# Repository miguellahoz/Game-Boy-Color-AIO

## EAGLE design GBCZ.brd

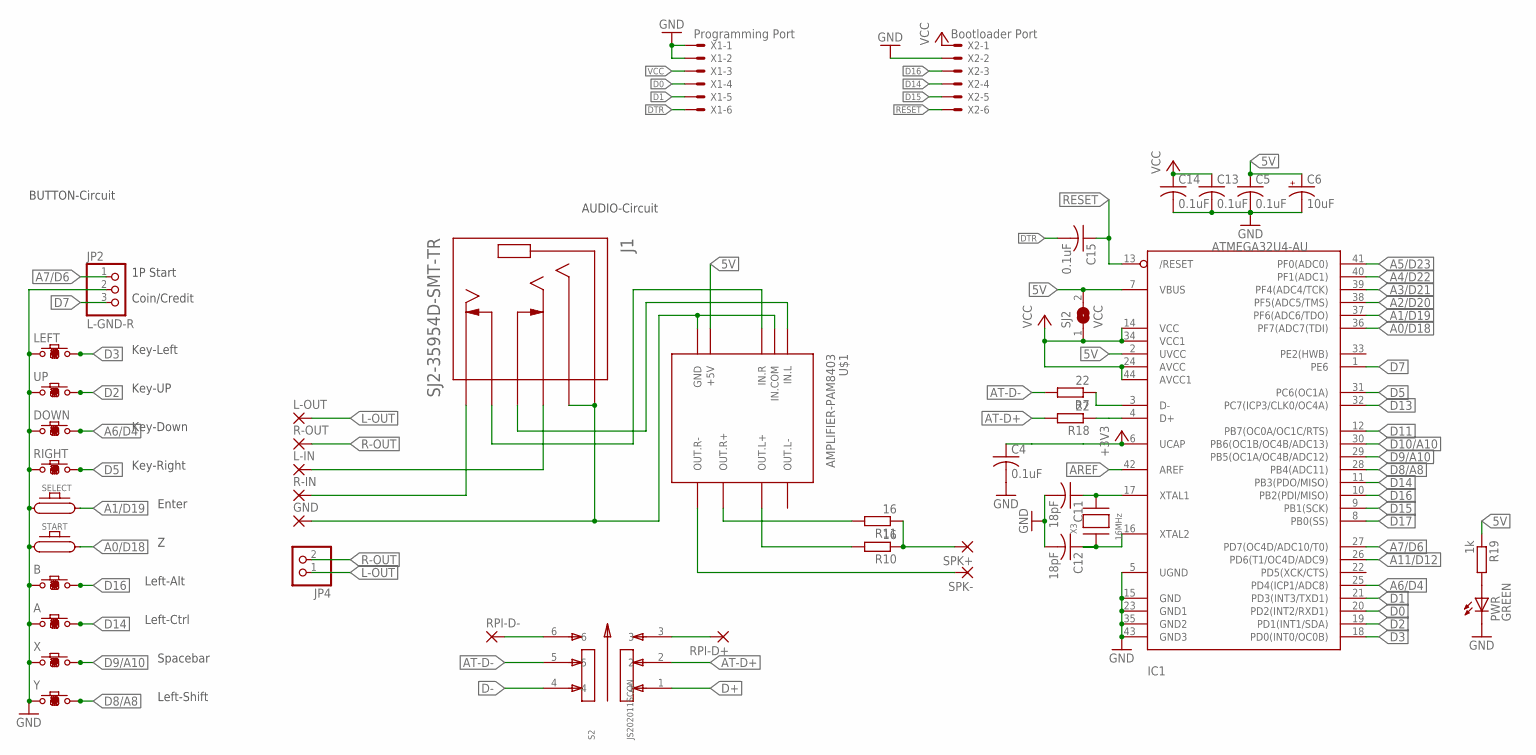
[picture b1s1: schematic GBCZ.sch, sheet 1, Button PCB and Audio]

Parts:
A: GBC_BTN
B: GBC_BTN
C4, C5, C13, C14, C15: 0.1uF; C0805K
C6: 10uF; A/3216-18R
C11, C12: 18pF; C0805K
DOWN: GBC_BTN
GND: WIREPADSMD1,27-254; SMD1,27-2,54
IC1: ATMEGA32U4-AU; TQFP44
J1: SJ2-35954D-SMT-TR; CUI_SJ2-35954D-SMT-TR
JP2: L-GND-R; 1X03
JP4: PINHD-1X2; 1X02
L-IN: WIREPADSMD1,27-254; SMD1,27-2,54
L-OUT: WIREPADSMD1,27-254; SMD1,27-2,54
LEFT: GBC_BTN
PWR: GREEN; CHIPLED_0805
R7, R18: 22; R0603
R10, R11: 16; R0603
R19: 1k; R0603
R-IN: WIREPADSMD1,27-254; SMD1,27-2,54
R-OUT: WIREPADSMD1,27-254; SMD1,27-2,54
RIGHT: GBC_BTN
RPI-D+: WIREPADSMD1,27-254; SMD1,27-2,54
RPI-D-: WIREPADSMD1,27-254; SMD1,27-2,54
S2: JS202011SCQN; SW_JS202011SCQN
SELECT: GBC_BTN_START
SJ2: VCC; SJ
SPK+: WIREPADSMD1,27-254; SMD1,27-2,54
SPK-: WIREPADSMD1,27-254; SMD1,27-2,54
START: GBC_BTN_START
U$1: AMPLIFIER-PAM8403
UP: GBC_BTN
X: GBC_BTN
X1: Programming Port; 22-23-2061
X2: Bootloader Port; 22-23-2061
X3: 16MHz; NX5032
Y: GBC_BTN

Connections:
5V: C5.1, C6.+, IC1.2 (UVCC), IC1.7 (VBUS), R19.1, SJ2.2, U$1.+5V; also elsewhere on the board
+3V3: C4.1, IC1.6 (UCAP)
A0/D18: IC1.36 (PF7(ADC7(TDI)), START.P$2
A1/D19: IC1.37 (PF6(ADC6/TDO)), SELECT.P$2
A2/D20: IC1.38 (PF5(ADC5/TMS))
A3/D21: IC1.39 (PF4(ADC4/TCK))
A4/D22: IC1.40 (PF1(ADC1))
A5/D23: IC1.41 (PF0(ADC0))
A6/D4: DOWN.P$2, IC1.25 (PD4(ICP1/ADC8))
A7/D6: IC1.27 (PD7(OC4D/ADC10/T0)), JP2.1
A11/D12: IC1.26 (PD6(T1/OC4D/ADC9))
AREF: IC1.42 (AREF)
AT-D+: R18.2, S2.2
AT-D-: R7.2, S2.5
D0: IC1.20 (PD2(INT2/RXD1)), X1.4
D1: IC1.21 (PD3(INT3/TXD1)), X1.5
D2: IC1.19 (PD1(INT1/SDA)), UP.P$2
D3: IC1.18 (PD0(INT0/OC0B)), LEFT.P$2
D5: IC1.31 (PC6(OC1A)), RIGHT.P$2
D7: IC1.1 (PE6), JP2.3
D8/A8: IC1.28 (PB4(ADC11)), Y.P$2
D9/A10: IC1.29 (PB5(OC1A/OC4B/ADC12)), X.P$2
D10/A10: IC1.30 (PB6(OC1B/OC4B/ADC13))
D11: IC1.12 (PB7(OC0A/OC1C/RTS))
D13: IC1.32 (PC7(ICP3/CLK0/OC4A))
D14: A.P$2, IC1.11 (PB3(PDO/MISO)), X2.4
D15: IC1.9 (PB1(SCK)), X2.5
D16: B.P$2, IC1.10 (PB2(PDI/MISO)), X2.3
D17: IC1.8 (PB0(SS))
D+: S2.1; also elsewhere on the board
D-: S2.4; also elsewhere on the board
DTR: C15.2, X1.6
GND: A.P$1, B.P$1, C4.2, C5.2, C6.-, C11.2, C12.2, C13.2, C14.2, DOWN.P$1, IC1.5 (UGND), IC1.15 (GND), IC1.23 (GND1), IC1.35 (GND2), IC1.43 (GND3), JP2.2, LEFT.P$1, PWR.C, RIGHT.P$1, SELECT.P$1, START.P$1, UP.P$1, X.P$1, X1.1, X1.2, X2.2, Y.P$1; also elsewhere on the board
L-OUT: JP4.1, L-OUT.1
unnamed: RPI-D-.1, S2.6
unnamed: RPI-D+.1, S2.3
unnamed: R11.2, U$1.OUT.R+
unnamed: GND.1, J1.1 (SLEEVE), J1.4 (RING2), U$1.GND, U$1.IN.COM
unnamed: J1.11 (RING1_SWITCH), U$1.IN.L
unnamed: J1.10 (TIP_SWITCH), U$1.IN.R
unnamed: J1.2 (TIP), R-IN.1
unnamed: J1.3 (RING1), L-IN.1
unnamed: R10.2, U$1.OUT.L+
unnamed: R10.1, R11.1, SPK+.1
unnamed: SPK-.1, U$1.OUT.R-
unnamed: IC1.3 (D-), R7.1
unnamed: IC1.4 (D+), R18.1
unnamed: C12.1, IC1.16 (XTAL2), X3.P$1
unnamed: C11.1, IC1.17 (XTAL1), X3.P$2
unnamed: PWR.A, R19.2
R-OUT: JP4.2, R-OUT.1
RESET: C15.1, IC1.13 (/RESET), X2.6
VCC: C13.1, C14.1, IC1.14 (VCC), IC1.24 (AVCC), IC1.34 (VCC1), IC1.44 (AVCC1), SJ2.1, X1.3; also elsewhere on the board

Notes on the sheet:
AUDIO-Circuit
BUTTON-Circuit
Key-UP
Key-Left
Key-Down
Key-Right
Left-Ctrl
Left-Alt
Spacebar
Left-Shift
Enter
Coin/Credit
1P Start

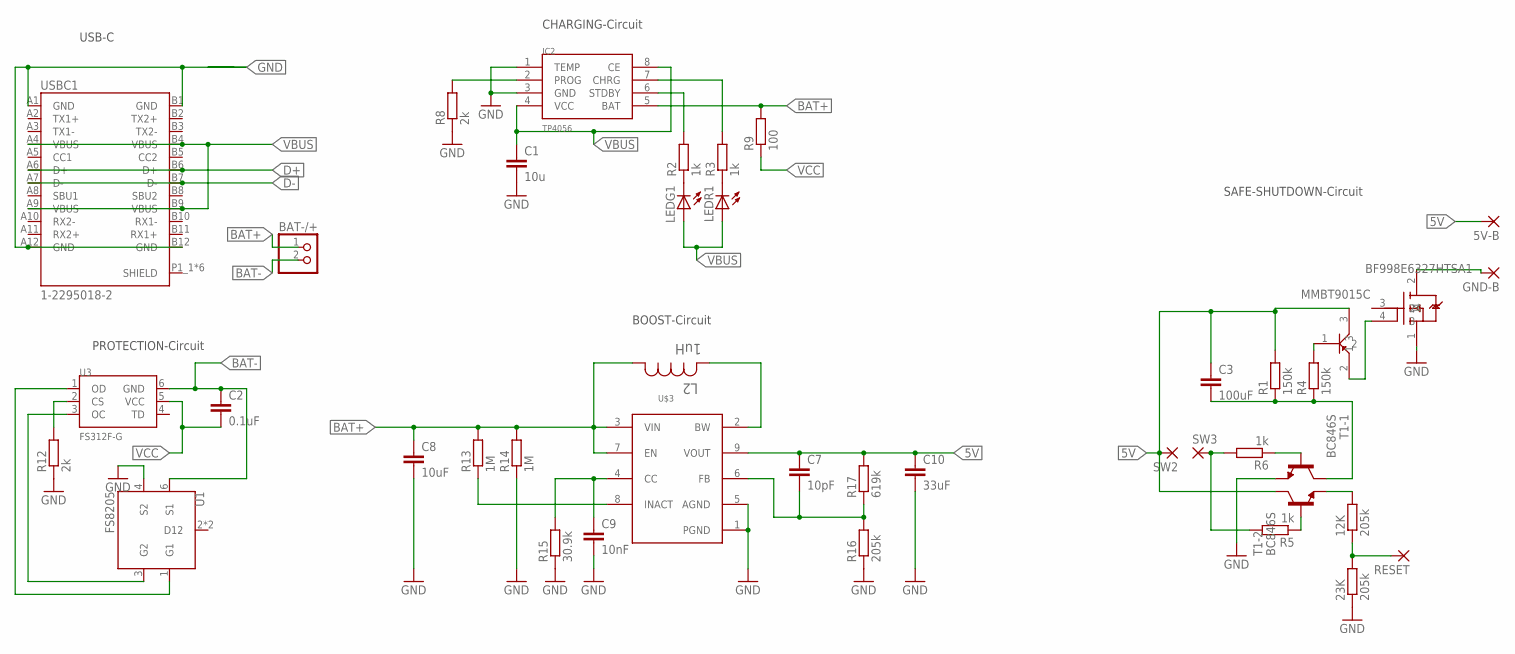
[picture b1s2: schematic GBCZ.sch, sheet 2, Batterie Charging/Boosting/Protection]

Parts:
5V-B: WIREPADSMD1,27-254; SMD1,27-2,54
12K, 23K: 205k; R0603
BAT-/+: PINHD-1X2; 1X02
BF998E6327HTSA1: INF-SOT143-4-1_V_1; INF-SOT143-4-1_V_1PRIMARY
C1: 10u; C0603
C2: 0.1uF; C0603
C3: 100uF; C1812
C7: 10pF; C1812
C8: 10uF; C1812
C9: 10nF; C1812
C10: 33uF; C1812
GND-B: WIREPADSMD1,27-254; SMD1,27-2,54
IC2: TP4056; SOP-8
L2: 1uH; INDM7676X435N
LEDG1: LEDCHIP-LED0603; CHIP-LED0603
LEDR1: LEDCHIP-LED0603; CHIP-LED0603
MMBT9015C: INF-SOT23_M_1; INF-SOT23_M_1PRIMARY
R1, R4: 150k; R0603
R2, R3, R5, R6: 1k; R0603
R8, R12: 2k; R0603
R9: 100; R0603
R13, R14: 1M; R0603
R15: 30.9k; R0603
R16: 205k; R0603
R17: 619k; R0603
RESET: WIREPADSMD1,27-254; SMD1,27-2,54
SW2, SW3: WIREPADSMD1,27-254; SMD1,27-2,54
T1: BC846S; SOT363
U1: FS8205; SOT23-6
U3: FS312F-G; SOT23-6
U$3: TPS61235RWLR; CONV_TPS61235RWLR
USBC1: 1-2295018-2; TE_1-2295018-2

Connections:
5V: 5V-B.1, C3.1, C7.1, C10.1, MMBT9015C.3 (1), R1.2, R17.2, SW2.1, T1.3 (C), U$3.9 (VOUT); also elsewhere on the board
BAT+: BAT-/+.1, C8.1, IC2.5 (BAT), L2.1, R9.2, R13.2, R14.2, U$3.3 (VIN), U$3.7 (EN)
BAT-: BAT-/+.2, C2.1, U1.6 (S1), U3.6 (GND)
D+: USBC1.A6 (D+), USBC1.B6 (D+); also elsewhere on the board
D-: USBC1.A7 (D-), USBC1.B7 (D-); also elsewhere on the board
GND: 23K.1, BF998E6327HTSA1.1 (4), C1.2, C8.2, C9.2, C10.2, IC2.1 (TEMP), IC2.3 (GND), R8.1, R12.1, R14.1, R15.1, R16.1, T1.1 (E), U1.4 (S2), U$3.1 (PGND), U$3.5 (AGND), USBC1.A1 (GND), USBC1.A12 (GND), USBC1.B1 (GND), USBC1.B12 (GND); also elsewhere on the board
unnamed: BF998E6327HTSA1.2 (1), GND-B.1
unnamed: BF998E6327HTSA1.4 (3), MMBT9015C.2 (3)
unnamed: MMBT9015C.1 (2), R4.2
unnamed: 12K.2, T1.4 (E)
unnamed: C3.2, R1.1, R4.1, T1.6 (C)
unnamed: R6.1, T1.2 (B)
unnamed: R5.2, R6.2, SW3.1
unnamed: R5.1, T1.5 (B)
unnamed: R13.1, U$3.8 (INACT)
unnamed: C9.1, R15.2, U$3.4 (CC)
unnamed: IC2.6 (STDBY), R2.2
unnamed: IC2.7 (CHRG), R3.2
unnamed: LEDG1.C, R2.1
unnamed: L2.2, U$3.2 (BW)
unnamed: LEDR1.C, R3.1
unnamed: C7.2, R16.2, R17.1, U$3.6 (FB)
unnamed: IC2.2 (PROG), R8.2
unnamed: U1.3 (G2), U3.3 (OC)
unnamed: U1.1 (G1), U3.1 (OD)
unnamed: R12.2, U3.2 (CS)
unnamed: 12K.1, 23K.2, RESET.1
VBUS: C1.1, IC2.4 (VCC), IC2.8 (CE), LEDG1.A, LEDR1.A, USBC1.A4 (VBUS), USBC1.A9 (VBUS), USBC1.B4 (VBUS), USBC1.B9 (VBUS)
VCC: C2.2, R9.1, U3.5 (VCC); also elsewhere on the board

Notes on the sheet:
BOOST-Circuit
PROTECTION-Circuit
CHARGING-Circuit
SAFE-SHUTDOWN-Circuit
USB-C

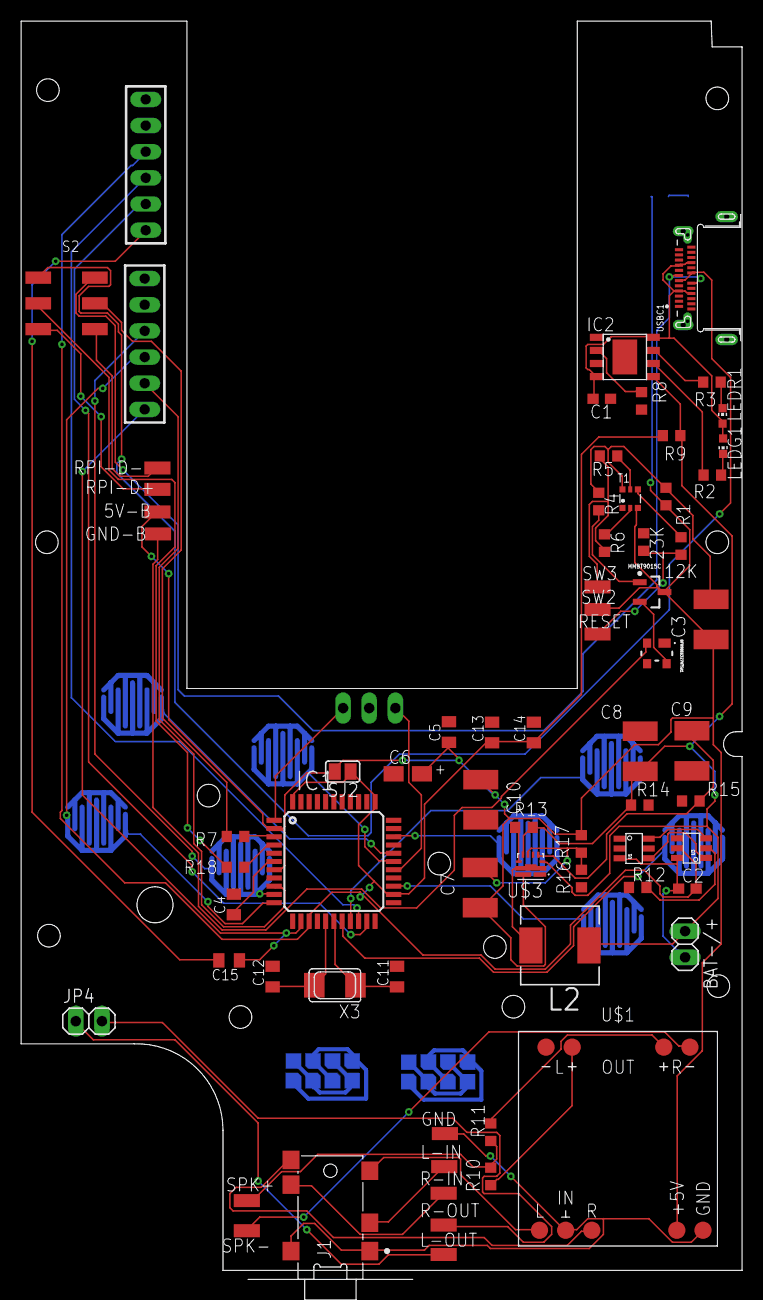
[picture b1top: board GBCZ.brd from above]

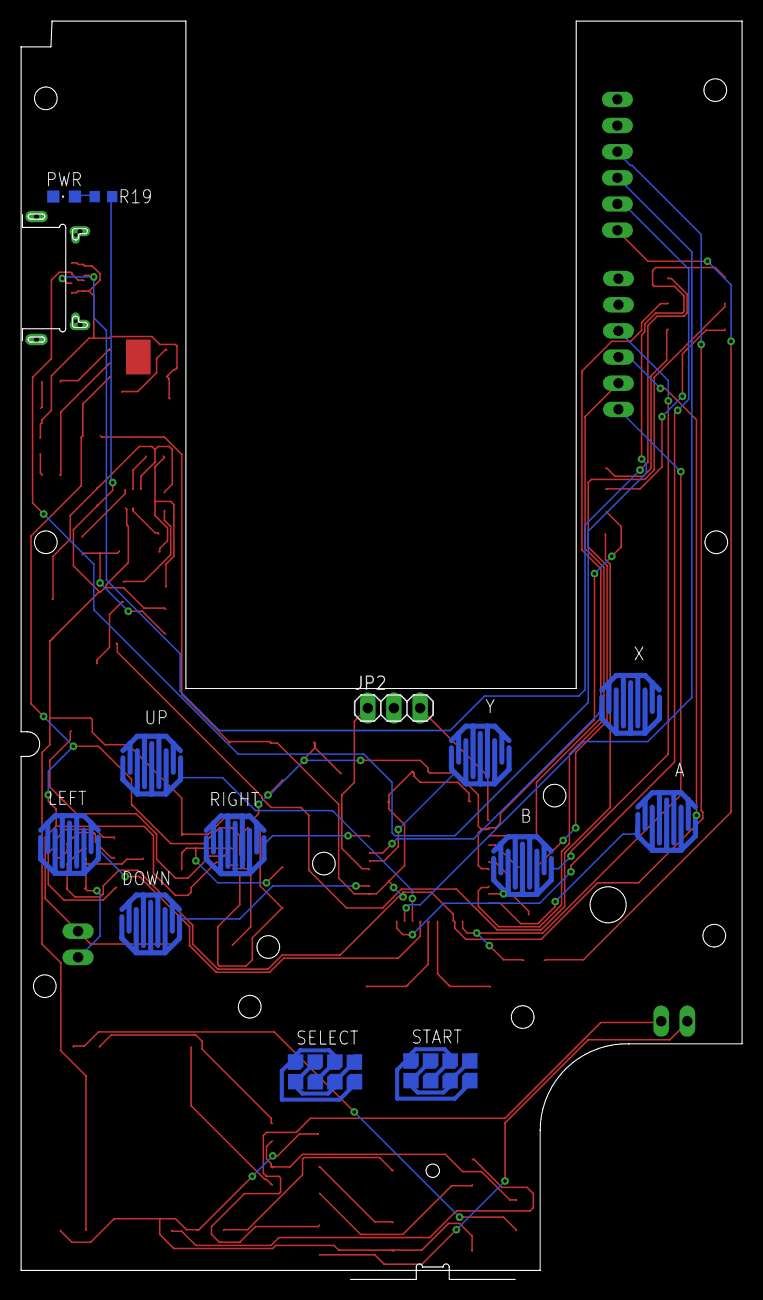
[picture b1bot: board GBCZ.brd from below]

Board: 2 copper layers, 70.0 x 122.1 mm, 83 parts (13 on the bottom side), 67 nets.

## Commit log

2019-01-03 Added first files
2019-01-03 Images of the gerber files

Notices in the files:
parts and their libraries:
diy-modules: Released under the Creative Commons Attribution 4.0 International License: http://creativecommons.org/licenses/by/4.0
